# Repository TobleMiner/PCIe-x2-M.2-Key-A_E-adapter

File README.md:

PCIe 2x M.2 A/E Key adapter
===========================

This adapter supports large-size M.2 Key A/E cards with two PCIe lanes.
It has been specifically designed for power-hungry 802.11ax 4x4 MIMO
cards with unusual form factors.

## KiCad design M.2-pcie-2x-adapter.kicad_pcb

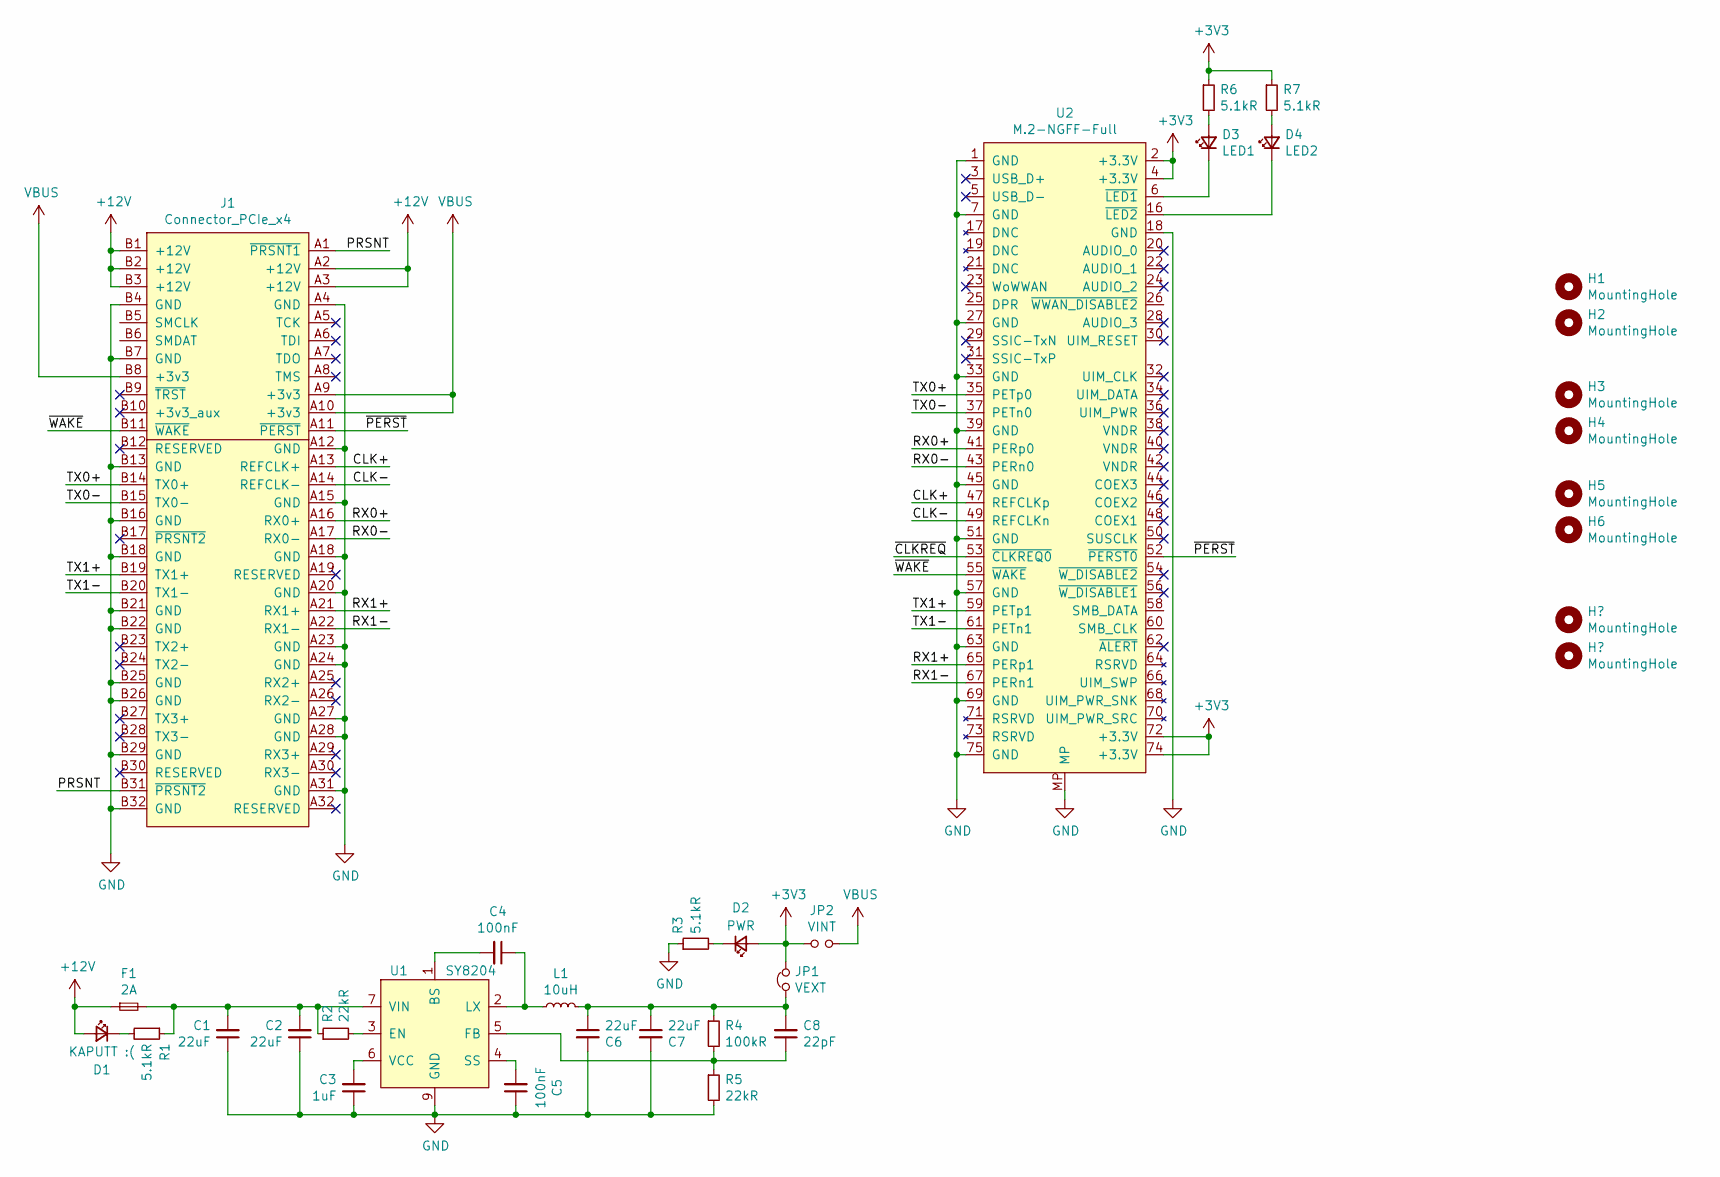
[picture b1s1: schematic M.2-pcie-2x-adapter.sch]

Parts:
C1, C2, C6, C7: 22uF; C_0805_2012Metric; LCSC C45783
C3: 1uF; C_0402_1005Metric; LCSC C52923
C4, C5: 100nF; C_0402_1005Metric
C8: 22pF; C_0402_1005Metric
D1: KAPUTT :(; LED_0603_1608Metric; LCSC C2286
D2: PWR; LED_0603_1608Metric; LCSC C72043
D3: LED1; LED_0603_1608Metric; LCSC C72038
D4: LED2; LED_0603_1608Metric; LCSC C2290
F1: 2A; Fuse_Littelfuse-NANO2-451_453; LCSC C99547
H1, H2: MountingHole; MountingHole_3.2mm_M3_Pad_Via
H3, H4, H5, H6: MountingHole; MountingHole_2.2mm_M2_Pad_Via
J1: Connector_PCIe_x4; BUS_PCIexpress_x4
JP1: VEXT; SolderJumper-2_P1.3mm_Bridged_Pad1.0x1.5mm
JP2: VINT; SolderJumper-2_P1.3mm_Open_Pad1.0x1.5mm
L1: 10uH; L_Sumida_CDMC6D28_7.25x6.5mm; LCSC C167223
R1, R3, R6, R7: 5.1kR; R_0402_1005Metric; LCSC C25905
R2, R5: 22kR; R_0402_1005Metric; LCSC C25768
R4: 100kR; R_0402_1005Metric; LCSC C25741
U1: SY8204; HSOP-8-1EP_3.9x4.9mm_P1.27mm_EP2.41x3.1mm_ThermalVias; LCSC C125895
U2: M.2-NGFF-Full; MDTXXXXXX001

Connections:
+3V3: D2.2 (A), JP1.2, JP2.2, R6.1, R7.1, U2.2 (+3.3V), U2.4 (+3.3V), U2.72 (+3.3V), U2.74 (+3.3V)
+12V: D1.2 (A), F1.1, J1.A2 (+12V), J1.A3 (+12V), J1.B1 (+12V), J1.B2 (+12V), J1.B3 (+12V)
/CLK+: J1.A13 (REFCLK+), U2.47 (REFCLKp)
/CLK-: J1.A14 (REFCLK-), U2.49 (REFCLKn)
/PRSNT: J1.A1 (~PRSNT1), J1.B31 (~PRSNT2)
/RX0+: J1.A16 (RX0+), U2.41 (PERp0)
/RX0-: J1.A17 (RX0-), U2.43 (PERn0)
/RX1+: J1.A21 (RX1+), U2.65 (PERp1)
/RX1-: J1.A22 (RX1-), U2.67 (PERn1)
/TX0+: J1.B14 (TX0+), U2.35 (PETp0)
/TX0-: J1.B15 (TX0-), U2.37 (PETn0)
/TX1+: J1.B19 (TX1+), U2.59 (PETp1)
/TX1-: J1.B20 (TX1-), U2.61 (PETn1)
/~CLKREQ: U2.53 (~CLKREQ0)
/~PERST: J1.A11 (~PERST), U2.52 (~PERST0)
/~WAKE: J1.B11 (~WAKE), U2.55 (~WAKE)
GND: C1.1, C2.1, C3.1, C5.1, C6.2, C7.2, J1.A4 (GND), J1.A12 (GND), J1.A15 (GND), J1.A18 (GND), J1.A20 (GND), J1.A23 (GND), J1.A24 (GND), J1.A27 (GND), J1.A28 (GND), J1.A31 (GND), J1.B4 (GND), J1.B7 (GND), J1.B13 (GND), J1.B16 (GND), J1.B18 (GND), J1.B21 (GND), J1.B22 (GND), J1.B25 (GND), J1.B26 (GND), J1.B29 (GND), J1.B32 (GND), R3.1, R5.2, U1.9 (GND), U2.1 (GND), U2.7 (GND), U2.18 (GND), U2.27 (GND), U2.33 (GND), U2.39 (GND), U2.45 (GND), U2.51 (GND), U2.57 (GND), U2.63 (GND), U2.69 (GND), U2.75 (GND), U2.MP
unnamed: C3.2, U1.6 (VCC)
unnamed: C4.1, L1.1, U1.2 (LX)
unnamed: C4.2, U1.1 (BS)
unnamed: C5.2, U1.4 (SS)
unnamed: C6.1, C7.1, C8.2, JP1.1, L1.2, R4.1
unnamed: C8.1, R4.2, R5.1, U1.5 (FB)
unnamed: D1.1 (K), R1.2
unnamed: D2.1 (K), R3.2
unnamed: D3.1 (K), U2.6 (~LED1)
unnamed: D3.2 (A), R6.2
unnamed: D4.1 (K), U2.16 (~LED2)
unnamed: D4.2 (A), R7.2
unnamed: R2.2, U1.3 (EN)
VBUS: J1.A9 (+3v3), J1.A10 (+3v3), J1.B8 (+3v3), JP2.1
VIN: C1.2, C2.2, F1.2, R1.1, R2.1, U1.7 (VIN), U1.8 (VIN)

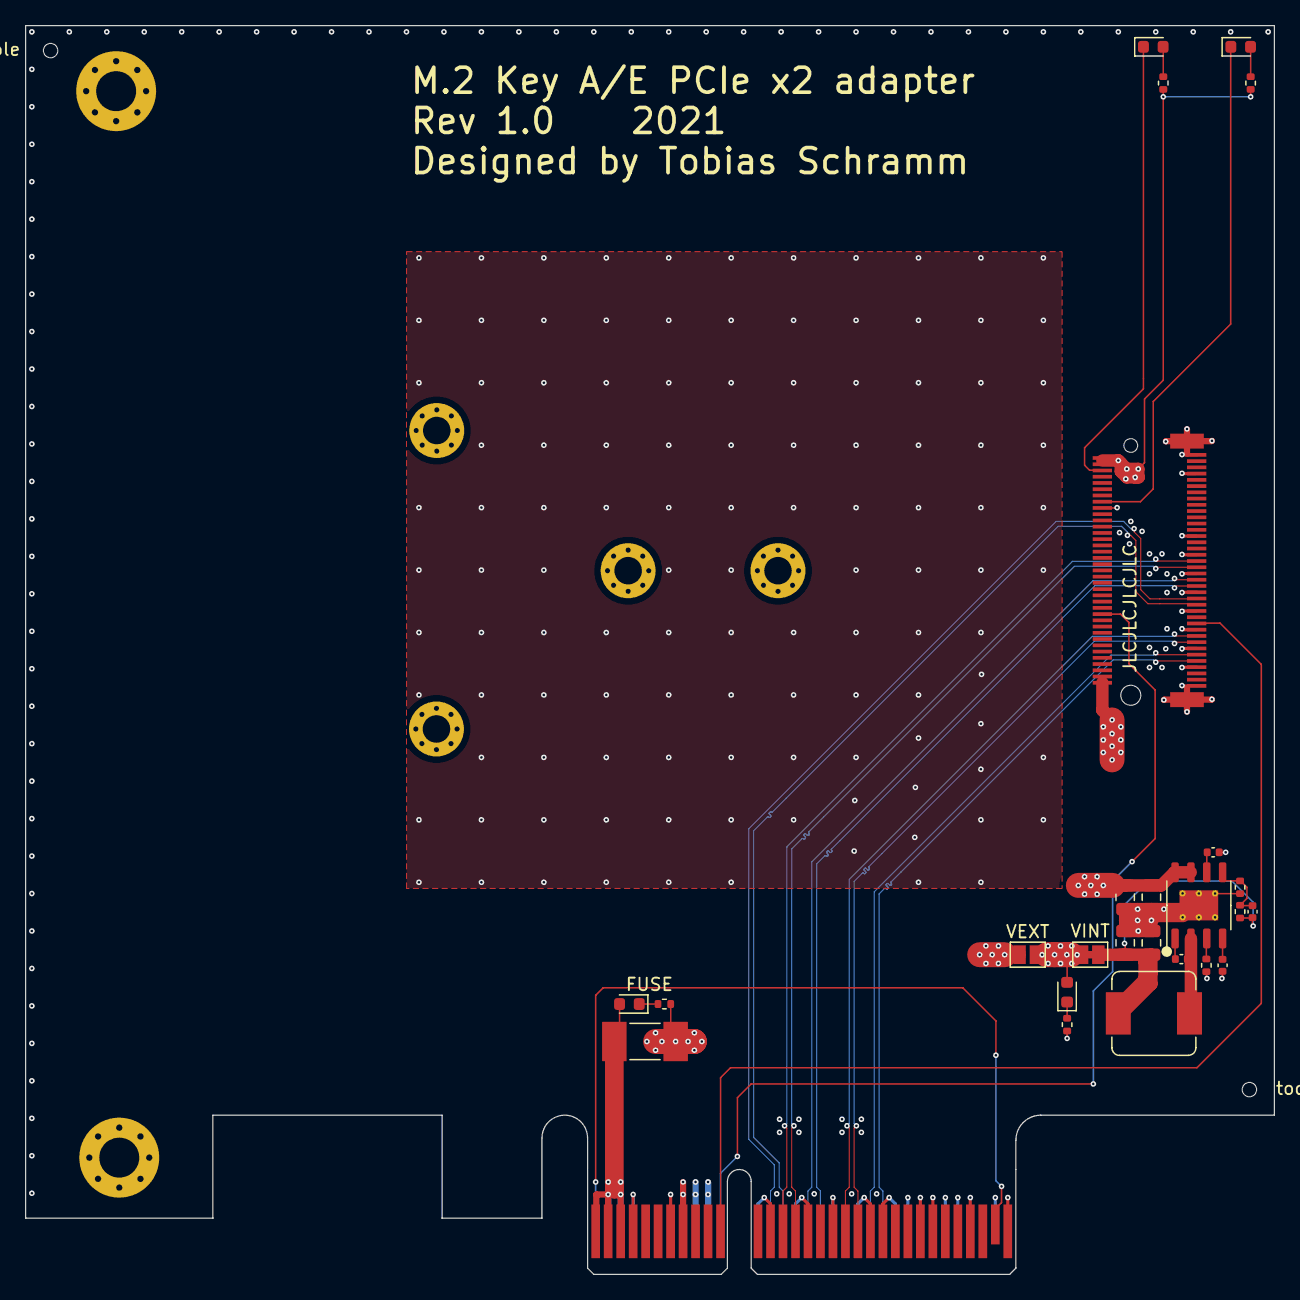
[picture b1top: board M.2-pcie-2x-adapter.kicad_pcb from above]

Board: 4 copper layers, 100.0 x 100.0 mm, 34 parts (0 on the bottom side), 31 nets.

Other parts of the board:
H7, H8: MountingHole; ToolingHole_JLCSMT

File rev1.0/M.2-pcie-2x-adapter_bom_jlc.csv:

"Comment","Designator","Footprint","LCSC Part #"
"22uF","C2,C1,C6,C7","C_0805_2012Metric","C45783"
"1uF","C3","C_0402_1005Metric","C52923"
"100nF","C4,C5","C_0402_1005Metric","C1525"
"22pF","C8","C_0402_1005Metric","C1555"
"KAPUTT :(","D1","LED_0603_1608Metric","C2286"
"PWR","D2","LED_0603_1608Metric","C72043"
"LED1","D3","LED_0603_1608Metric","C72038"
"LED2","D4","LED_0603_1608Metric","C2290"
"2A","F1","Fuse_Littelfuse-NANO2-451_453","C99547"
"10uH","L1","L_Sumida_CDMC6D28_7.25x6.5mm","C167223"
"100kR","R4","R_0402_1005Metric","C25741"
"22kR","R5,R2","R_0402_1005Metric","C25768"
"5.1kR","R6,R7,R1,R3","R_0402_1005Metric","C25905"
"SY8204","U1","HSOP-8-1EP_3.9x4.9mm_P1.27mm_EP2.41x3.1mm_ThermalVias","C125895"

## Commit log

2021-10-16 Prepare for production
2021-10-16 Add README
2021-10-16 Add 3D models to all parts
2021-10-16 Add rev1.0 artifacts
